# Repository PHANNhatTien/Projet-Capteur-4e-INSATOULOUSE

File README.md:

# Projet-Capteur-4e-INSATOULOUSE
Ce projet s'inscrit dans l'UF "Du capteur au banc de test" en 4ème année au département de Génie Physique de l'INSA Toulouse.
# 2021-2022_Paccard_Lemaire_Projet_Capteur
Ce projet s'inscrit dans l'UF **"Du capteur au banc de test"** en 4ème année au département de Génie Physique de l'INSA Toulouse.
***
L'objectif de ce dernier est d'élaborer un **capteur de déformation** low-tech à base de graphite. L'application d'une contrainte mécanique sur un capteur en papier sur lequel un dépôt de crayon à papier à été fait, modifie la distance entre les particules de graphite. La conductivité électrique de la couche de graphite est elle aussi modifiée et celà induit une variation de la résistance. C'est cette donnée qui va nous intéresser.

L'ensemble des étapes menées pour réaliser ce capteur, en allant du **design** jusqu'à la **réalisation** en passant par le **codage** seront détaillées dans ce dossier.

## Sommaire
* [1. Description du projet et détail des livrables](#PremiereSection)
* [2. Matériel nécessaire](#DeuxiemeSection)
* [3. Arduino](#TroisiemeSection)
  * [3.1. Librairies utilisées](#TroisiemeSection1)
  * [3.2. Code Arduino](#TroisiemeSection1)
* [4. Application Android](#QuatriemeSection)
* [5. KiCad](#CinquiemeSection)
  * [5.1. Symboles et empreintes des composants](#CinquiemeSection1)
  * [5.2. Schématique](#CinquiemeSection2)
  * [5.3. Placement des composants](#CinquiemeSection3)
  * [5.4. Visualisation 3D](#CinquiemeSection4)
* [6. Fabrication du shield](#SixiemeSection)
  * [6.1. Réalisation du PCB](#SixiemeSection1)
  * [6.2. Perçage et soudure](#SixiemeSection2)
* [7. Simulation](#SeptiemeSection)
* [8. Tests et résultats](#HuigtiemeSection)
  * [8.1. Banc de test](#HuigtiemeSection1)
  * [8.2. Résultats obtenus](#HuigtiemeSection2)
  * [8.3. Analyse des résultats et pistes d'améliorations](#HuigtiemeSection3)
* [9. Datasheet](#NeuviemeSection)
* [Contacts](#DixiemeSection)

## 1. Détail des livrables et description du projet 
Voici l'ensemble des livrables du projet :
- Un **shield PCB** se connectant à une carte **Arduino UNO** contenant un amplificateur transimpédance, un module bluetooth, un écran OLED et un encodeur rotatoire
- Un **code Arduino** permettant de mesurer la déformation du capteur et de piloter le module bluetooth, l'écran OLED et l'encodeur rotatoire
- Une **application Android APK**
- Un **protocole de test** 
- La **datasheet** du capteur de déformation

Tout d'abord, nous avons réalisé un code Arduino permettant de vérifier notre montage contenant un amplificateur transimpédance, un écran OLED, un module bluetooth et un encodeur rotatoire. Une fois le montage fonctionnel, nous avons réalisé le design de notre shield sur le logiciel *KiCad*. Nous l'avons ensuite fabriqué et assemblé (lithographie, perçage, soudage des composants, etc.). En parallèle de cela, nous avons utilisé le logiciel *MIT App Inventor* afin de développer une application Android APK, capable de communiquer et recevoir les informations envoyées par le module bluetooth telles que les valeurs de résistance du capteur mesurées. Nous avons par la suite mis en place un banc de test pour pour caractériser les différents types de capteurs en fonction de leur déformation et de la mine de crayon utilisée (HB, B, 9B, etc.). Enfin, nous avons établi une datasheet à l'aide des résulats obtenus par le banc de test.

## 2. Matériel nécessaire
Pour réaliser le capteur ainsi que le PCB associé, voici la liste des composants nécessaires :
* x2 résistance 100kΩ
* x1 résistance 10kΩ
* x2 résistance 1kΩ
* x1 capacité 1μF
* x3 capacité 100nF
* x1 amplificateur opérationnel LTC1050
* x1 module Bluetooth HC05
* x1 encodeur rotatoire KY_040
* x1 écran OLED I2C 0.91

## 3. Arduino 
### 3.1. Librairies utilisées 
Nous avons utilisé différentes librairies dans notre code Arduino. La librarie ["Adafruit_SSD1306"](/Libraries/Adafruit_SSD1306) permet de contrôller l'écran OLED. La librairie ["Adafruit_BusIO"](/Libraries/Adafruit_busIO) permet de gérer la connexion en I2C et SPI.

### 3.2. Code Arduino 
[Deux codes Arduino](https://github.com/MOSH-Insa-Toulouse/2021-2022_Paccard_Lemaire_Projet_Capteur/tree/main/Arduino) ont été développés sous Arduino IDE pour profiter au mieux des fonctionnalités de notre capteur.

#### Code Graphite_sensor
Le [premier code](https://github.com/MOSH-Insa-Toulouse/2021-2022_Paccard_Lemaire_Projet_Capteur/blob/main/Arduino/Graphite_sensor/Graphite_sensor.ino) permet d'assurer la communication entre la carte Arduino, qui récupère la valeur de tension renvoyée par le capteur, et les différents éléments ajoutés sur le shield soit : l'écran OLED, le module bluetooth et l'encodeur rotatoire. Différents menus sont accessibles sur l'écran OLED :
* Le premier menu permet un simple affichage de la résistance
* Le deuxième menu permet de selectionner le calibre de la résistance affichée sur le menu 1. Cette dernière peut ainsi être affichée en Ω, kΩ ou MΩ.
* Le troisème menu est un chronomètre permettant de savoir le temps d'execution du programme. C'est à dire le temps depuis le programme à été démarré.
* Le quatrième menu permet l'affichage d'une image.

En parallèle, le module bluetooth envoie les données de tension et de résistance à une application mobile qui sera détaillée dans la partie suivante.

#### Code Angle_calibration
Le [second code](https://github.com/MOSH-Insa-Toulouse/2021-2022_Paccard_Lemaire_Projet_Capteur/blob/main/Arduino/Angle_calibration/Angle_calibration.ino) Arduino permet d'effectuer un calcul d'angle par rapport à la calibration du capteur. L'utilisateur rentre les valeurs de la résistance à plat et à la position la plus courbée possible en appuyant sur le bouton poussoir présent sur l'encodeur rotatoire. En considérant la variation de résistance linéaire, un produit en croix est ensuite fait pour asssocier une valeur de résistance à un angle de déformation.

## 4. Application Android 

Nous avons réalisé une [application Android](https://github.com/MOSH-Insa-Toulouse/2021-2022_Paccard_Lemaire_Projet_Capteur/tree/main/Application%20bluetooth) grâce au site *MIT App Inventor* afin d'instaurer une communication entre notre module bluetooth HC-05 et un smartphone Android. Cette application possède différentes fonctionnalités : après avoir choisi dans un menu l'appareil auquel on souhaite se connecter, et que la connexion a été effectuée, différentes informations sont affichées sur l'écran du téléphone. En premier, on trouve la tension VADC en volts de sortie du circuit, elle est envoyée sous forme d'un byte à l'application depuis la carte Arduino, puis elle est reconvertie dans le code de l'application en float permettant d'afficher les décimales. C'est ensuite la valeur de la résistance du capteur en graphite qui est affichée en Méga Ohms, la valeur est directement calculée depuis l'application à partir de la valeur de VADC reconvertie en float. Finalement, la variation de la valeur de résistance est tracée en fonction du temps dans un graphique (canva) au-dessous. Nous avons enregistré un graphique avec uniquement des axes et leurs titres sous forme d'image que nous avons ensuite mis en fond du graphique pour le tracé. 

## 5. KiCad 
### 5.1. Symboles et empreintes des composants 
* Amplificateur LTC1050

* Ecran OLED

* Encodeur rotatoire KY_040

* Module bluetooth HC05

### 5.2. Schématique 
<p align="center">

Une fois les empreintes créées, nous avons réalisé le schéma de notre shield. En haut à droite sont représentées les broches de la carte Arduino. En haut au milieu est représenté l'amplificateur transimpédance et en bas du schématique se trouvent l'écran OLED, le module bluetooth et l'encodeur rotatoire.

### 5.3. Placement des composants 
<p align="center">

### 5.4. Visualisation 3D 
<p align="center">

## 6. Fabrication du shield 

### 6.1. Réalisation du PCB  
Le PCB a été réalisé au sein des départements de Génie Physique (GP) et Génie Électrique et Informatique (GEI) de l'INSA Toulouse avec l'aide de Catherine Crouzet. Notre PCB à été fabriqué à partir d'une plaquette d'epoxy recouverte d'une fine couche de cuivre (environ 60μm). 
Nous avons imprimé sur du papier calque la modélisation de notre PCB effectuée sur le logiciel *KICAD* pour ensuite insoler aux UV notre plaquette avec la silouhette par-dessus pendant quelques minutes. À l'aide d'un révelateur, nous avons retiré la partie de la résine non insolée.
La plaquette d'expoxy est ensuite placée dans un bain de perchlorure de fer pour la gravure, opération durant 7 minutes. Le cuivre non protégé par la résine est ainsi retiré de la plaquette ce qui nous permet d'obtenir le PCB avec les pistes souhaitées.
Enfin, de l'acétone est appliquée sur la plaquette pour éliminer les dernières traces de résine.

### 6.2. Perçage et soudure  
Nous avons ensuite percé notre PCB aux endroits où les différents composants seront insérés à l'aide d'une perceuse électrique. Le diamètre des trous dépend des différents composants à placer :
* ⌀ 0.8mm : AOP LTC1050, résistances et capacités
* ⌀ 1.0mm : Broches de connexion de la carte Arduino Uno et headers des différents modules (OLED, bluetooth, encodeur rotatoire)
* ⌀ 1.2mm : Broches de connexion du capteur de déformation

Notre PCB ayant été imprimé en face avant, certains composants ont été placé en face avant et d'autres en face arrière pour faciliter la soudure et la connexion à la carte Arduino Uno.

## 7. Simulation  
Nous avons simulé notre amplificateur transimpédance sur le logiciel *LTSpice* afin de savoir le comportement que notre circuit aura une fois branché à de réelles valeurs de tension. Les différentes simulations réalisées sur le logiciel nous ont permis d'une part de vérifier le bon fonctionnement du circuit et de chacun des composants intégrés, et d'autre part de comprendre l'utilité de chacun. Le détail de la démarche suivie et des résultats obtenus est disponible dans le document [Simulation_LTspice](https://github.com/MOSH-Insa-Toulouse/2021-2022_Paccard_Lemaire_Projet_Capteur/blob/main/Simulation_LTspice.pdf).

## 8. Tests et résultats  
### 8.1. Banc de test  
<p align="center">

Nous avons testé notre capteur sur un banc de test que nous avons conçu à partir de feuilles de papier épais. Nous avons fabriqué 7 cylindres de diamètre variable, allant de 5cm à 2cm par pas de 0,5cm.
En enrobant les différents cylindres avec notre capteur, nous appliquons une déformation maitrisée que nous pouvons calculer avec la formule : 
*ε = e / (2•R)*, avec ε la déformation, e l'épaisseur de notre capteur, et R le rayon de courbure appliqué soit le rayon de nos cylindres.

Nous avons décidé de réaliser des mesures de compression (graphite vers le cylindre) du capteur et pas en tension (graphite vers l'extérieur), car bien que ces deux méthodes soient possibles, les valeurs de  résistance renvoyées par notre capteur en tension n'étaient pas exploitables.

### 8.2. Résultats obtenus  
Les résultats complets de notre banc de test sont disponibles dans le dossier [Results](https://github.com/MOSH-Insa-Toulouse/2021-2022_Paccard_Lemaire_Projet_Capteur/tree/main/Results). 

### 8.3. Analyse des résultats et pistes d'améliorations  
En comprimant notre capteur, les particules de graphite se rapprochent les unes des autres, ce qui facilite la conduction dans le réseau percolé du système. De la même manière, en mettant notre capteur en tension, certains chemins de percolation se retrouvent brisés ce qui augmente la résistance du capteur.
En fonction du type de crayon utilisé, les variations relatives de résistance changent. En effet, plus le crayon est gras, c'est à dire qu'il dépose plus de graphite, moins sa variation relative de résistance est élevée. Cette caractéristique se vérifie sur nos [résultats](https://github.com/MOSH-Insa-Toulouse/2021-2022_Paccard_Lemaire_Projet_Capteur/tree/main/Results) et dans notre [datasheet](https://github.com/MOSH-Insa-Toulouse/2021-2022_Paccard_Lemaire_Projet_Capteur/blob/main/datasheet.pdf).
 
#### Comparaison avec le Flex-Sensor SEN-10264

 <p align="center">  
 <p align="center">
 
Nous avons étudié la réponse en résistance du flex-sensor SEN-10264 pour le comparer à nos capteurs low-tech à base de graphite. Nous avons observé que le flex-sensor industriel est plus sensible à la déformation (i.e. ΔR/R0 augmente plus rapidement avec la déformation) que nos capteurs de graphite lorsque l'on applique une déformation en tension. Cependant, en compression, le flex-sensor SEN-10264 possède une sensibilité du même ordre de grandeur que nos différents capteurs.
 
#### Pistes d'améliorations 
Certains point peuvent être améliorés dans notre projet :
* Le dépot de graphite sur le capteur est difficile à maîtriser et il est ainsi difficile de fabriquer plusieurs capteurs identiques
* Notre banc de test fourni des résultats répétables, il pourrait cependant être envisageable de fabriquer ce même banc de test en impression 3D pour augmenter sa résistance et longévitée.
* Sur notre PCB, l'ajout d'un potentiomètre digital permettrait de pouvoir travailler sur une gamme de résistance plus grande car ce dernier modulera la valeur de tension de sortie en fonction de la résistance du capteur

## 9. Datasheet  
La datasheet de notre capteur est disponible ici.

## Contacts  
Pour toutes questions relatives aux différentes parties du projet, que ce soit du KiCad au code Arduino, n'hésitez pas à nous contacter !
* PHAN Nhat Tien : ntphan@insa-toulouse.fr
* TRUONG Minh Thang : mttruong@insa-toulouse.fr

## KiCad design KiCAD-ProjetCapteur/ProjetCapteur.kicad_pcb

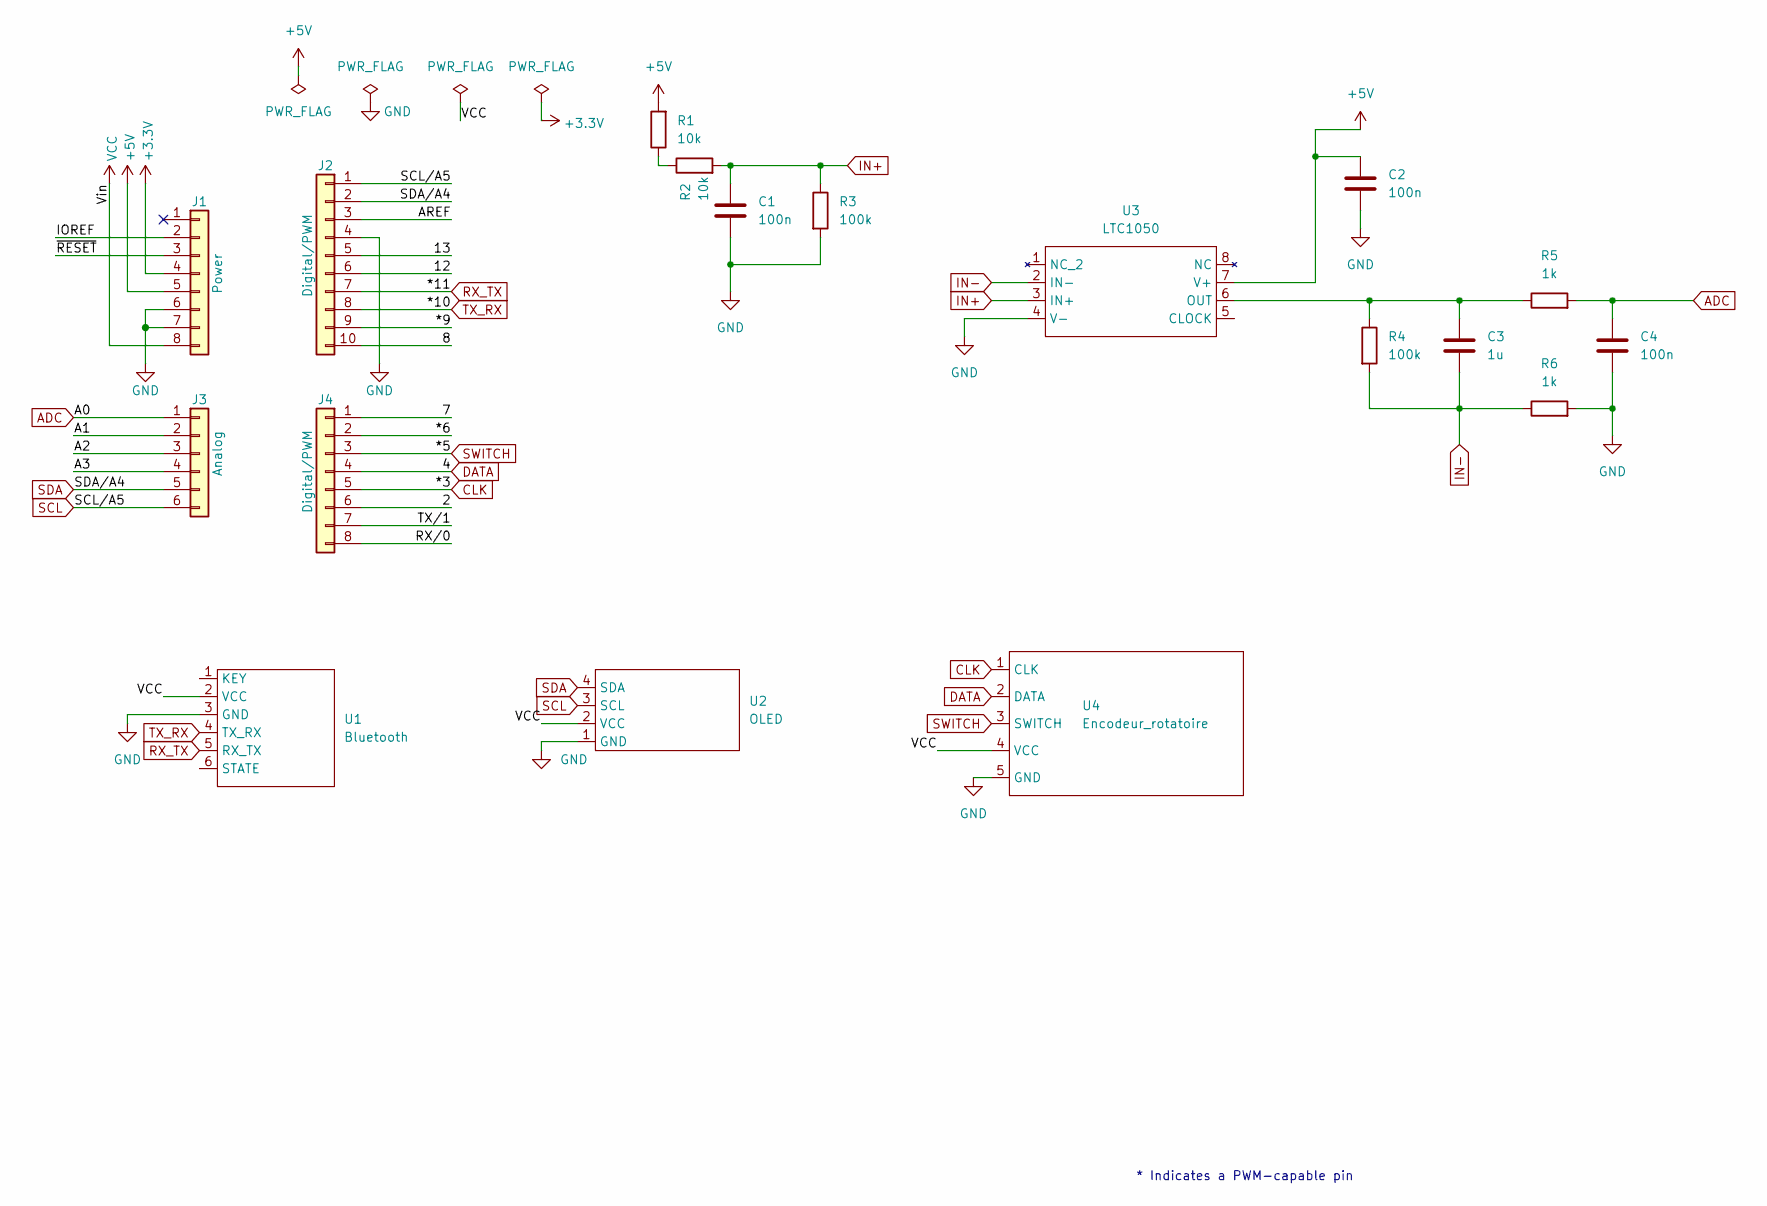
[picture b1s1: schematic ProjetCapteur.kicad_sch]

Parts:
C1, C2, C4: 100n; C_Disc_D5.0mm_W2.5mm_P5.00mm
C3: 1u; C_Rect_L9.0mm_W5.1mm_P7.50mm_MKT
J1: Power; PinSocket_1x08_P2.54mm_Vertical
J2: Digital/PWM; PinSocket_1x10_P2.54mm_Vertical
J3: Analog; PinSocket_1x06_P2.54mm_Vertical
J4: Digital/PWM; PinSocket_1x08_P2.54mm_Vertical
R1, R2: 10k; R_Axial_DIN0207_L6.3mm_D2.5mm_P7.62mm_Horizontal
R3, R4: 100k; R_Axial_DIN0207_L6.3mm_D2.5mm_P7.62mm_Horizontal
R5, R6: 1k; R_Axial_DIN0207_L6.3mm_D2.5mm_P7.62mm_Horizontal
U1: Bluetooth; BLUETOOTH_HC05
U2: OLED
U3: LTC1050
U4: Encodeur_rotatoire; KY_040

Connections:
+3V3: J1.4
+5V: C2.1, J1.5, R1.2, U3.7 (V+)
/2: J4.6
/8: J2.10
/12: J2.6
/13: J2.5
/*6: J4.2
/A1: J3.2
/A2: J3.3
/A3: J3.4
/AREF: J2.3
/IOREF: J1.2
/RX/0: J4.8
/TX/1: J4.7
/~RESET: J1.3
ADC: C4.1, J3.1, R5.2
CLK: J4.5, U4.1 (CLK)
DATA: J4.4, U4.2 (DATA)
GND: C1.2, C2.2, C4.2, J1.6, J1.7, J2.4, R3.2, R6.2, U1.3 (GND), U2.1 (GND), U3.4 (V-), U4.5 (GND)
IN+: C1.1, R2.2, R3.1, U3.3 (IN+)
IN-: C3.2, R4.2, R6.1, U3.2 (IN-)
unnamed: C3.1, R4.1, R5.1, U3.6 (OUT)
unnamed: R1.1, R2.1
RX_TX: J2.7, U1.5 (RX_TX)
SCL: J2.1, J3.6, U2.3 (SCL)
SDA: J2.2, J3.5, U2.4 (SDA)
SWITCH: J4.3, U4.3 (SWITCH)
TX_RX: J2.8, U1.4 (TX_RX)
VCC: J1.8, U1.2 (VCC), U2.2 (VCC), U4.4 (VCC)

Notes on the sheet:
* Indicates a PWM-capable pin

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
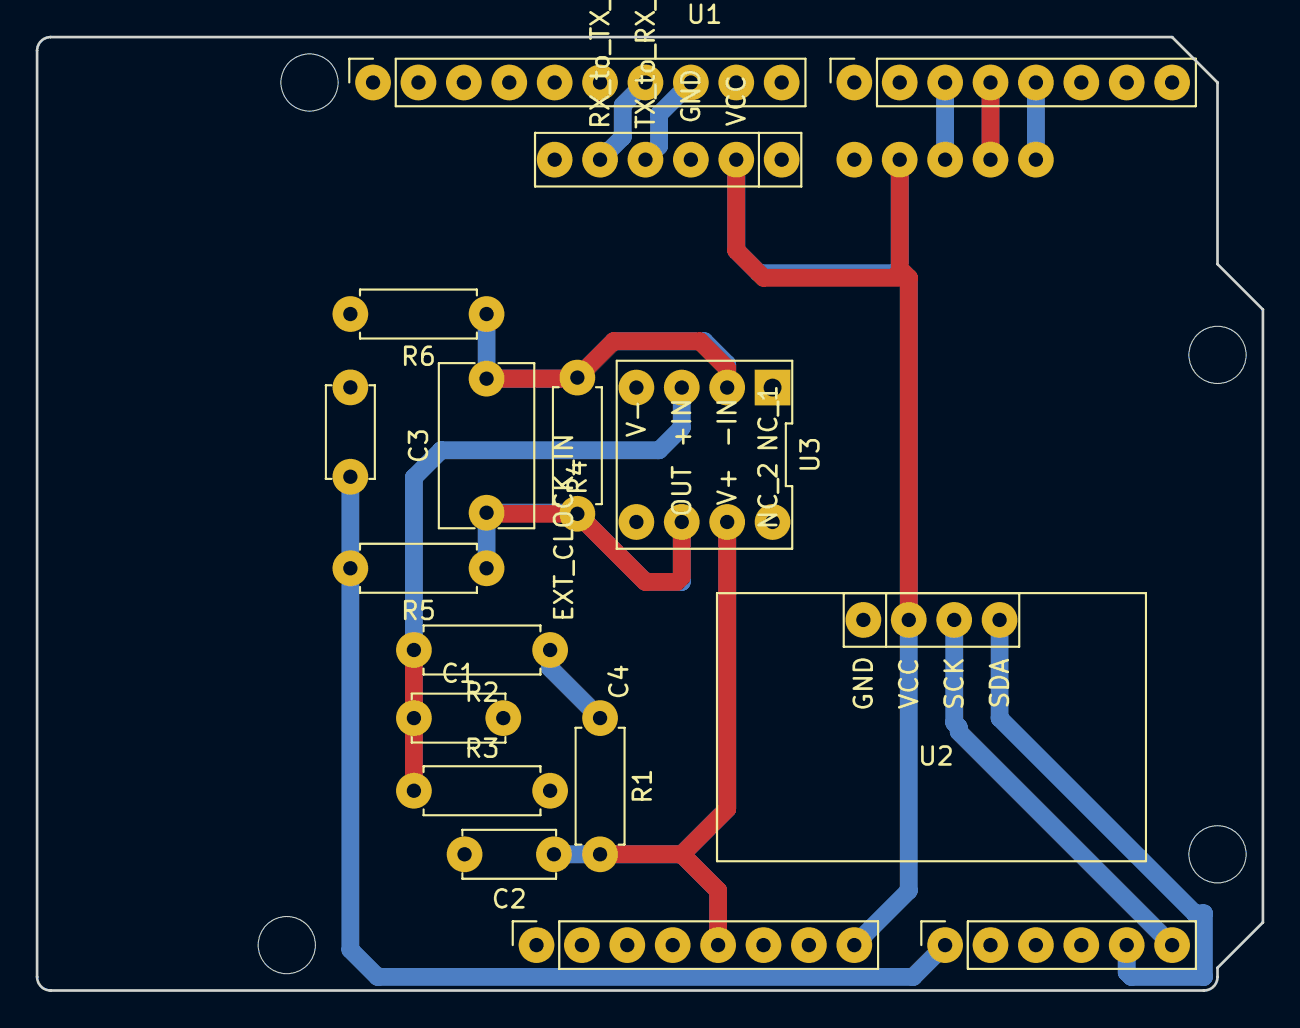
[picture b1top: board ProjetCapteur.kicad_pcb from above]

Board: 2 copper layers, 68.6 x 53.3 mm, 22 parts (1 on the bottom side), 16 nets.

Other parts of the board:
MH1, MH2, MH3, MH4: MountingHole_3.2mm

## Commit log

2023-04-13 Create Arduino
